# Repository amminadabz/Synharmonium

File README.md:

# The Synharmonium

#### is a new kind of musical instrument.
Designed to be easy to use, and more importantly, easy to make good music with. It uses the accordion's Stradella bass system to make it easy to play notes and chords that go well together, the Omnichord's strum plate to give texture to that harmony, and a piano keyboard for a familiar way to add a melody.

## A Well-Tempered synthesizer.
One of the goals of the Synharmonium is to create an instrument which uses an algorithmic implementation of just intonation. In other words, it tunes every note in a perfect mathematical relation to the root of whatever chord is being played. Where other instruments simply have every note an equal distance apart and call it done ("Equal Temperament"), the Synharmonium will ensure they are always in simple ratios to each other, allowing for a more resonant sound. But if you want to play _with_ those other instruments, you always have the option to disable this feature and return to the more common tuning.

## Digital where it's needed, analogue where it counts.
The Synharmonium uses a digital system to implement that tuning algorithm. But once the computer has decided what frequencies are best, everything that can analogue will be, including the envelope generators, drum machine oscillators, and effects. This allows it to have that classic analogue sound with none of the downsides.

But, if you want to use the Synharmonium's tuning technology with an external synthesizer, it also has full MIDI compatibility (with both DIN and USB).

## Free to build, modify, and hack
The hardware and software are all open source. I intend to base the control and tuning systems on an Arduino, which is beginner-friendly and hackable by design. I haven't the means to build these machines on a large scale at the moment (though I've thought about selling an "official version" as a preassembled machine and a kit, lmk what y'all think), so for the time being I will just be providing the design for free. That means you get to build it (!) until I know what I'm doing.

## A work in progress.
I'll be real with y'all: I don't know what I'm doing. Every part of this project is a skill that I am learning as I go. But I think this is a thing that deserves to exist, so I intend to let it. It will probably take some time, as I am currently pursuing degrees in Electrical Engineering and Computer Engineering, so I can only work on the Synharmonium in my free time.

If you have skills that could help this process along, feel free to join the project. Do [send me an email](mailto:uiwmusic@proton.me) first though, I'd like to know who I'm working with! 

Here goes nothin'!

-Evan

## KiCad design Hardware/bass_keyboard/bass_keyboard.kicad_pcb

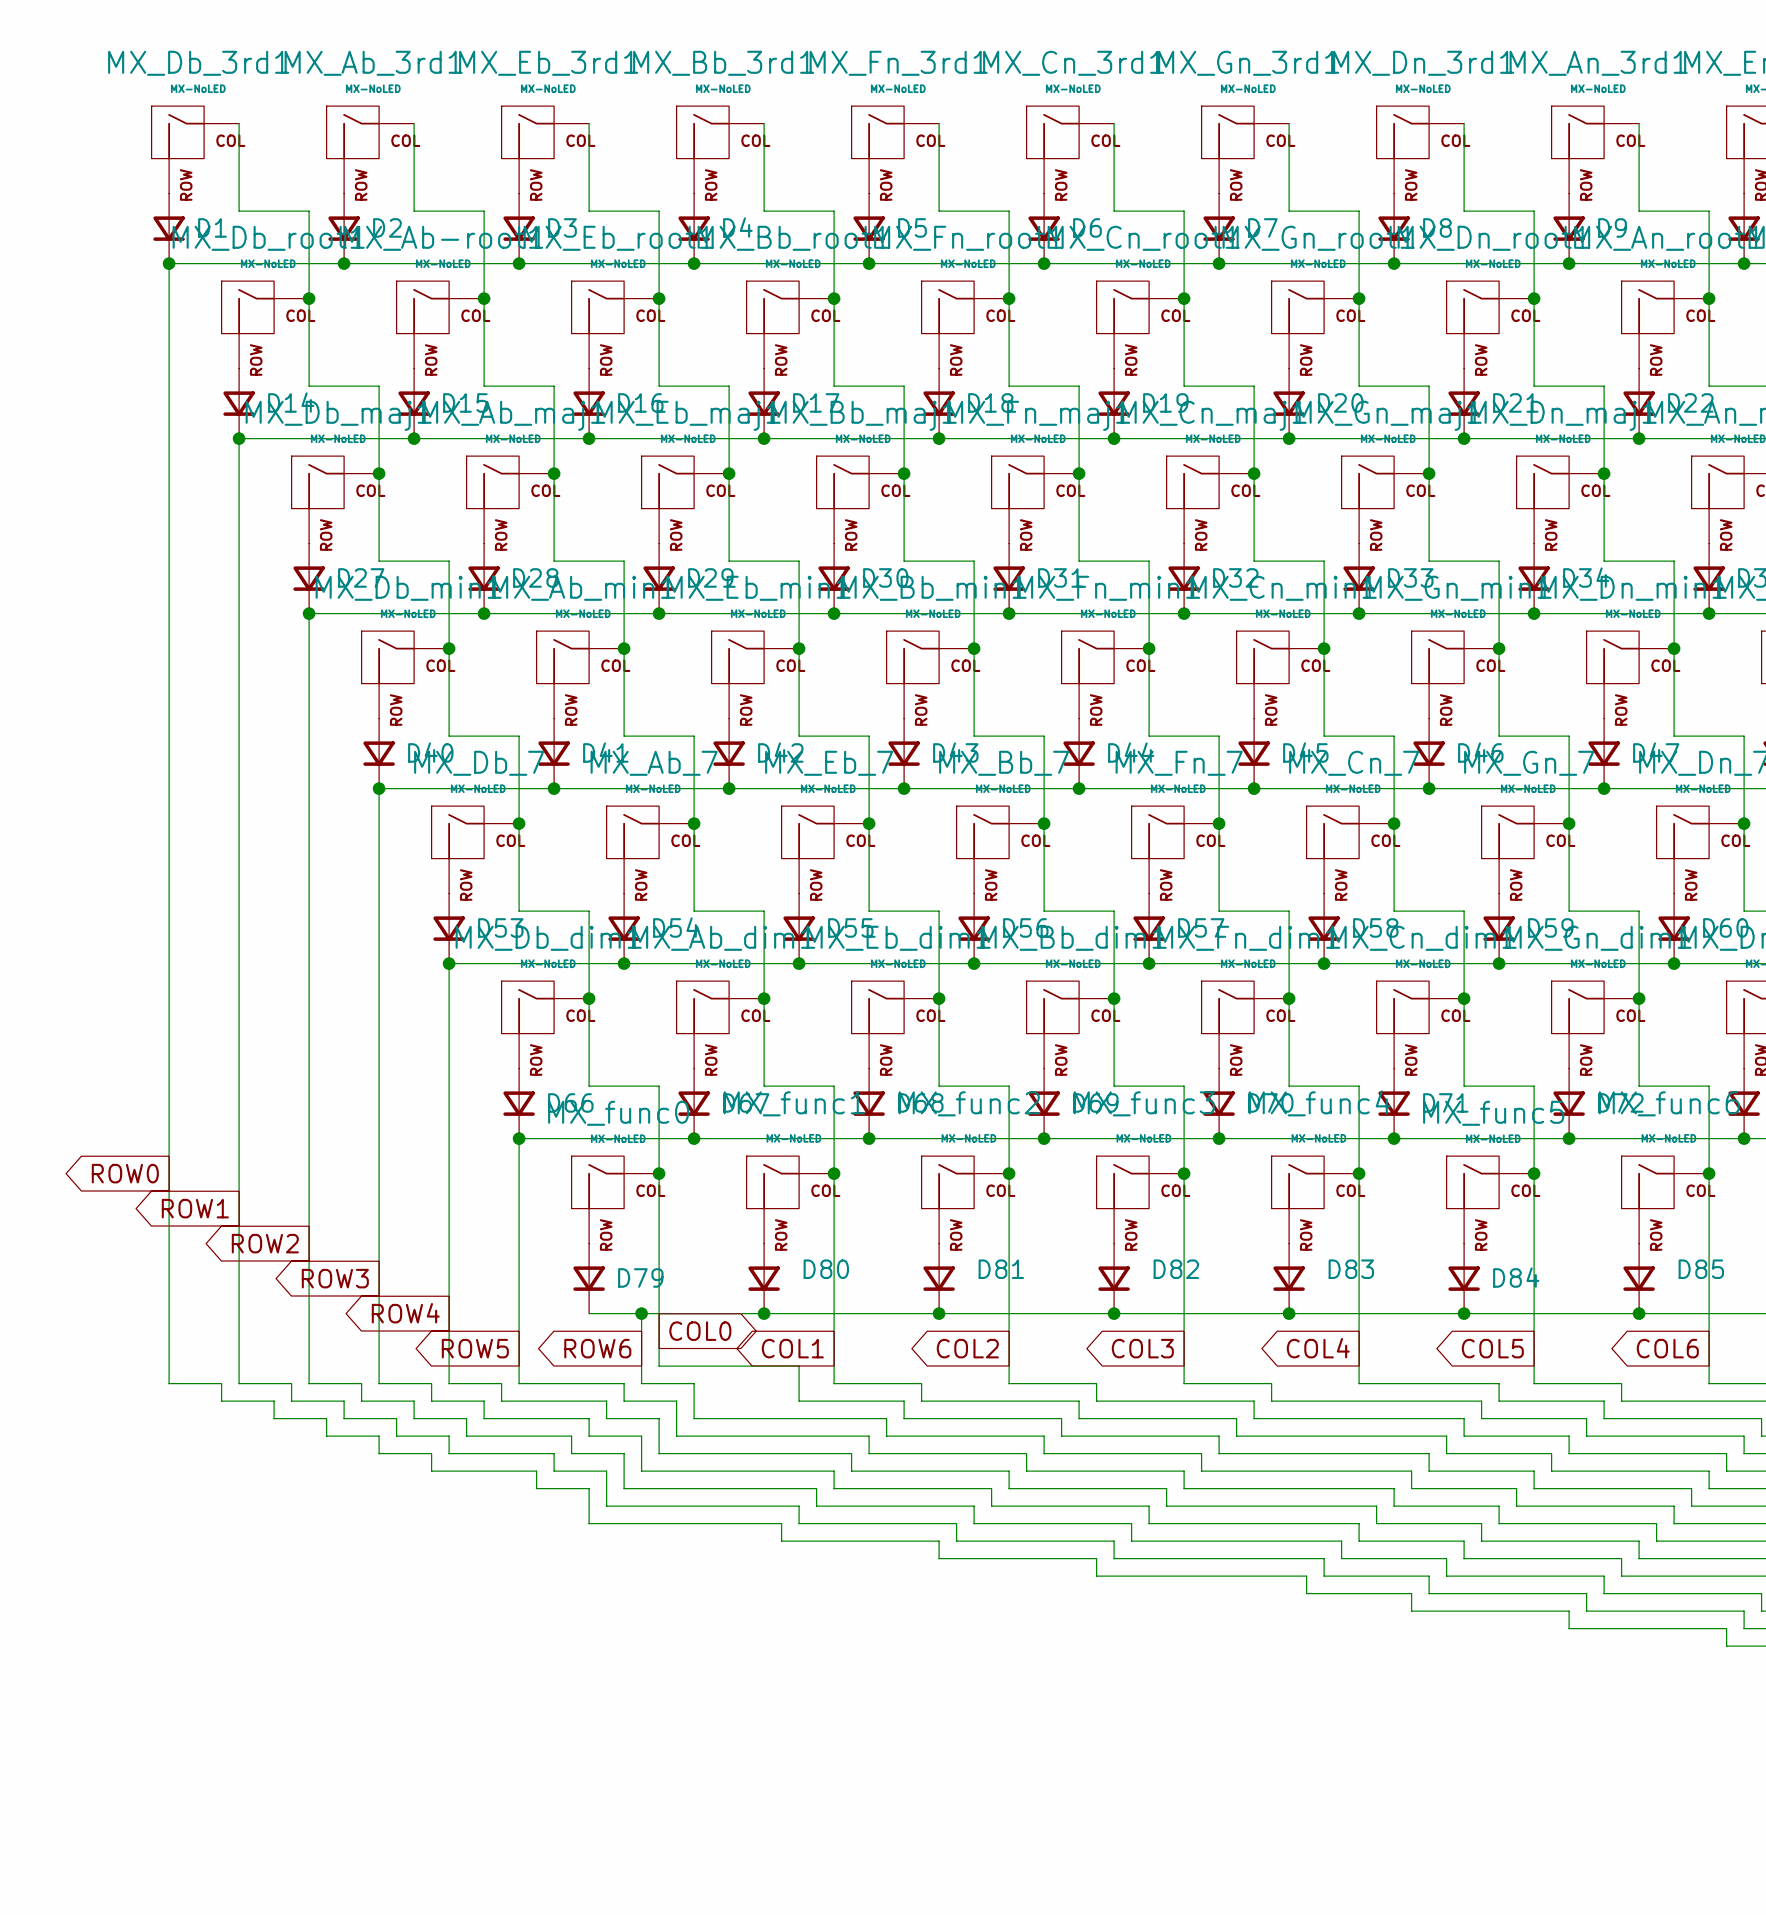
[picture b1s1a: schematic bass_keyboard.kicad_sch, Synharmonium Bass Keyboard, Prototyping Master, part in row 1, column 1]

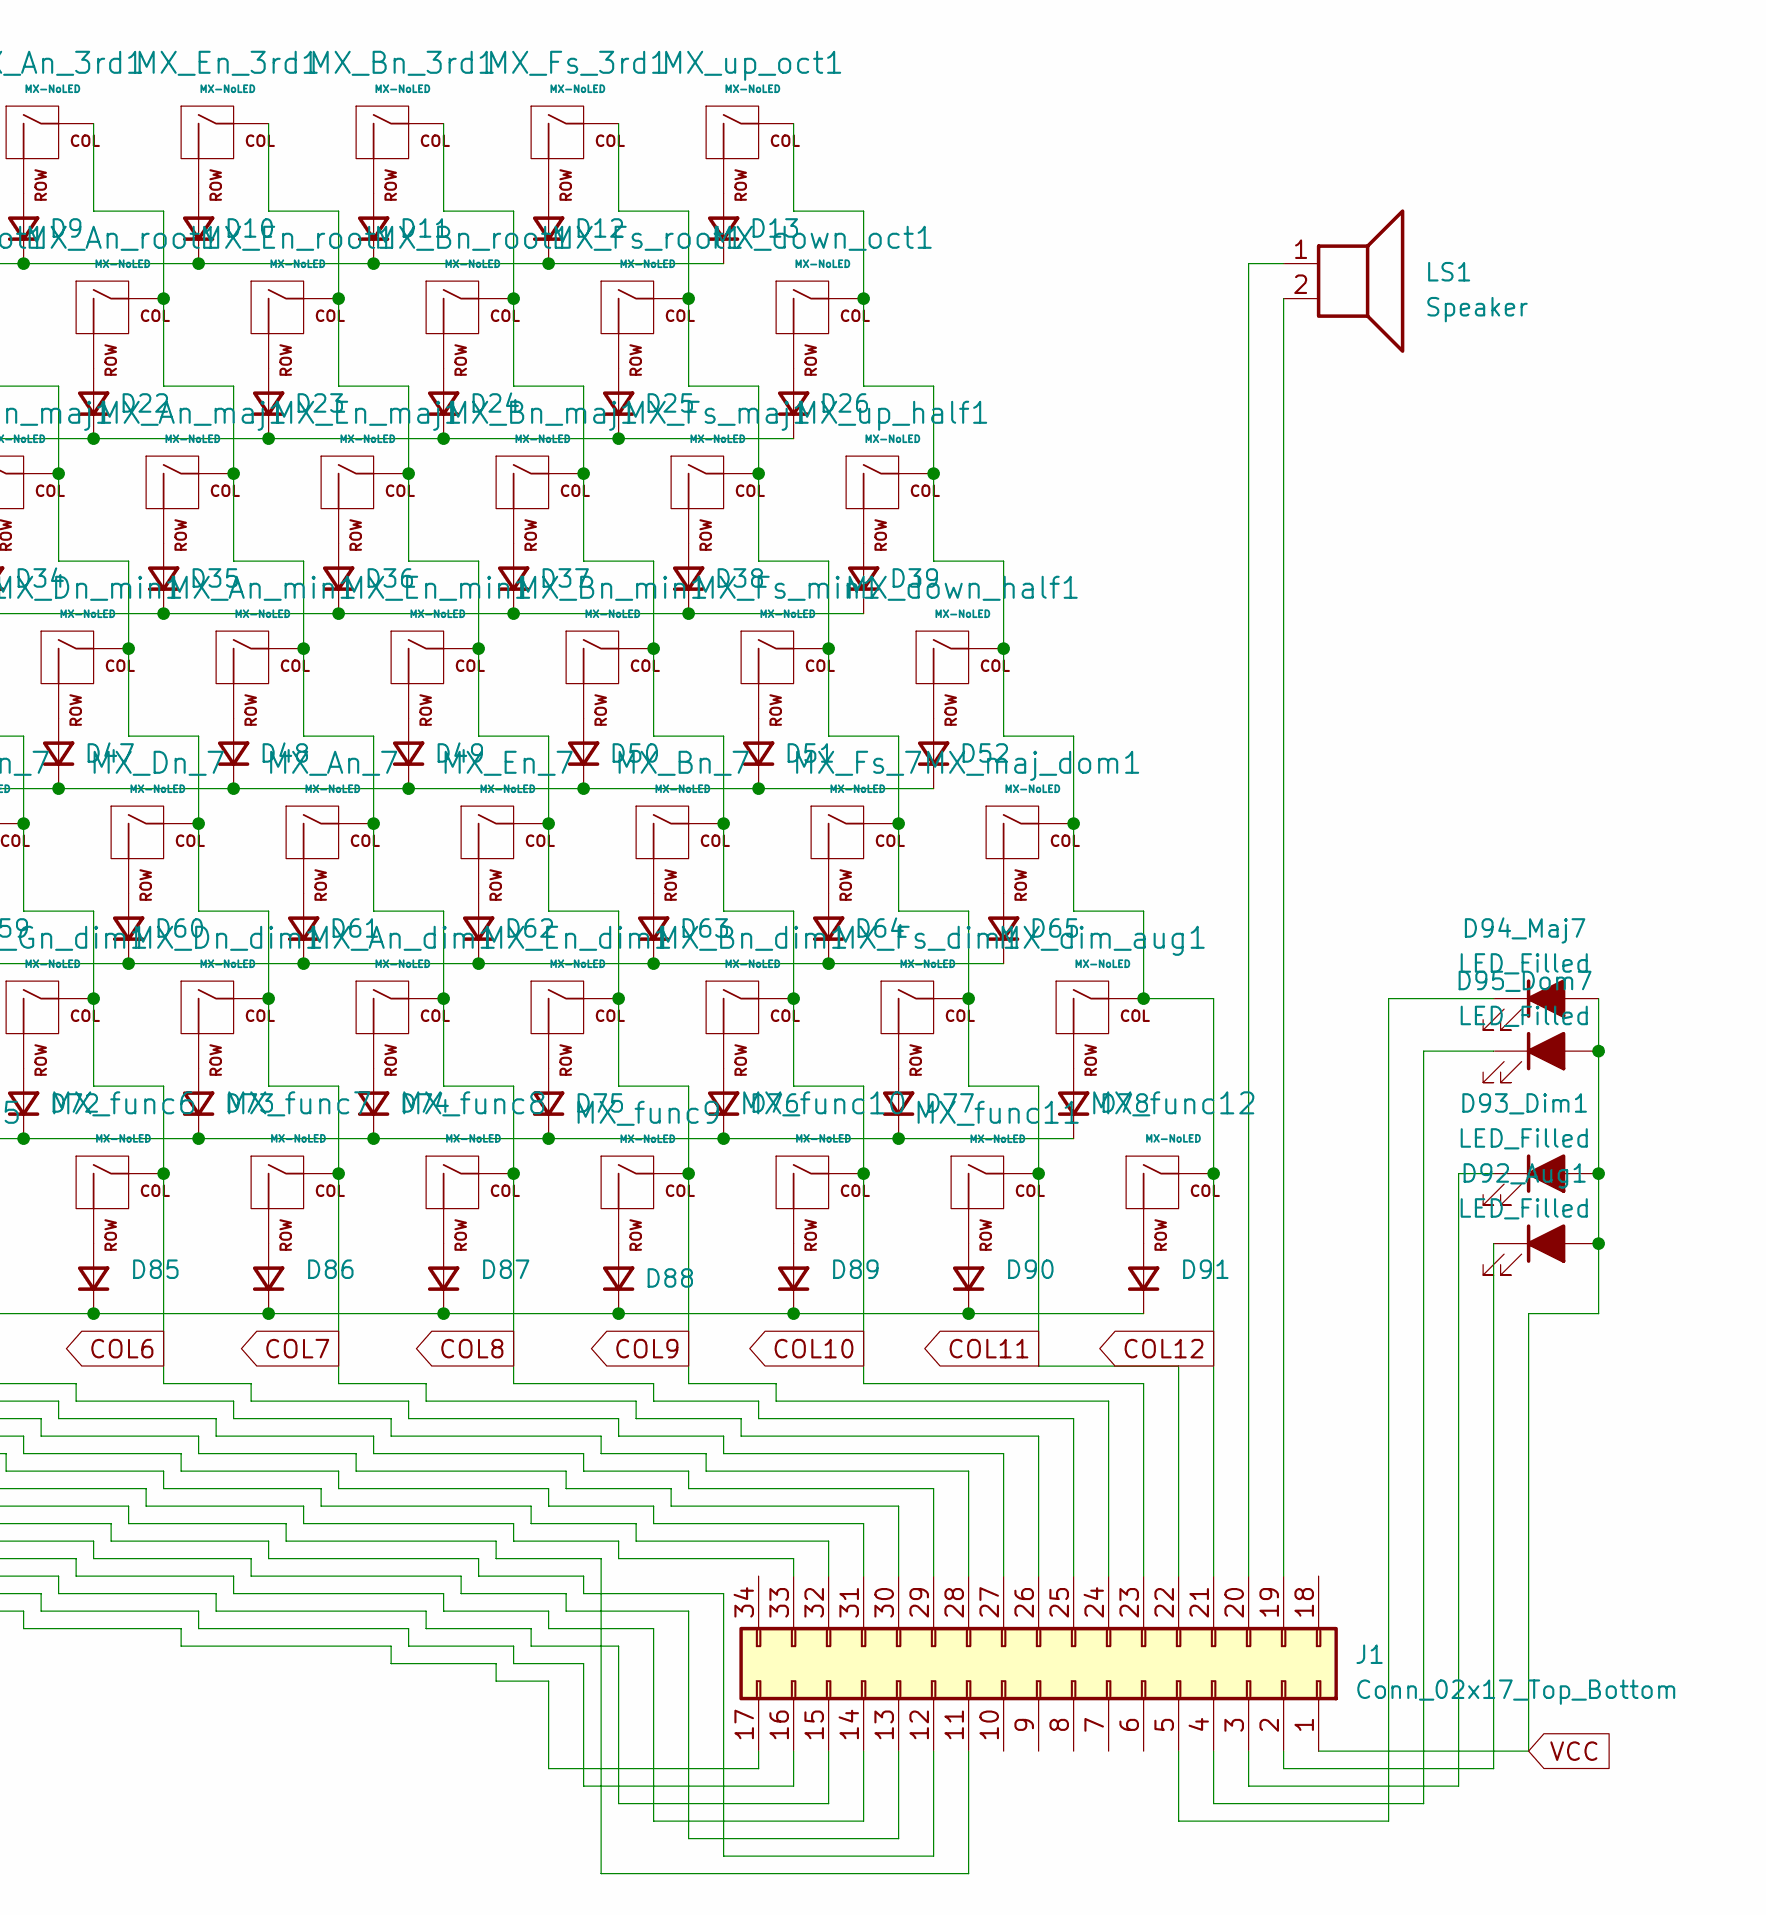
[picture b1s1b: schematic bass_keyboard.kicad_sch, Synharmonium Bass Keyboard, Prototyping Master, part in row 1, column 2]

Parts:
D1, D2, D3, D4, D5, D6, D7, D8, D9, D10, D11, D12, D13, D14, D15, D16, D17, D18, D19, D20, D21, D22, D23, D24, D25, D26, D27, D28, D29, D30, D31, D32, D33, D34, D35, D36, D37, D38, D39, D40, D41, D42, D43, D44, D45, D46, D47, D48, D49, D50, D51, D52, D53, D54, D55, D56, D57, D58, D59, D60, D61, D62, D63, D64, D65, D66, D67, D68, D69, D70, D71, D72, D73, D74, D75, D76, D77, D78, D79, D80, D81, D82, D83, D84, D85, D86, D87, D88, D89, D90, D91: D_Small; D_SOD-123
D92_Aug1, D93_Dim1, D94_Maj7, D95_Dom7: LED_Filled; LED_D3.0mm-Pretty
J1: Conn_02x17_Top_Bottom; IDC-Header_2x17_P2.54mm_Vertical
LS1: Speaker; SolderWire-1sqmm_1x02_P5.4mm_D1.4mm_OD2.7mm
MX_Ab-root1: MX-NoLED; SW_Cherry_MX_1.00u_PCB
MX_Ab_3rd1, MX_Ab_7: MX-NoLED; SW_Cherry_MX_1.00u_PCB
MX_Ab_dim1: MX-NoLED; SW_Cherry_MX_1.00u_PCB
MX_Ab_maj1: MX-NoLED; SW_Cherry_MX_1.00u_PCB
MX_Ab_min1: MX-NoLED; SW_Cherry_MX_1.00u_PCB
MX_An_3rd1, MX_An_7: MX-NoLED; SW_Cherry_MX_1.00u_PCB
MX_An_dim1: MX-NoLED; SW_Cherry_MX_1.00u_PCB
MX_An_maj1: MX-NoLED; SW_Cherry_MX_1.00u_PCB
MX_An_min1: MX-NoLED; SW_Cherry_MX_1.00u_PCB
MX_An_root1: MX-NoLED; SW_Cherry_MX_1.00u_PCB
MX_Bb_3rd1, MX_Bb_7: MX-NoLED; SW_Cherry_MX_1.00u_PCB
MX_Bb_dim1: MX-NoLED; SW_Cherry_MX_1.00u_PCB
MX_Bb_maj1: MX-NoLED; SW_Cherry_MX_1.00u_PCB
MX_Bb_min1: MX-NoLED; SW_Cherry_MX_1.00u_PCB
MX_Bb_root1: MX-NoLED; SW_Cherry_MX_1.00u_PCB
MX_Bn_3rd1, MX_Bn_7: MX-NoLED; SW_Cherry_MX_1.00u_PCB
MX_Bn_dim1: MX-NoLED; SW_Cherry_MX_1.00u_PCB
MX_Bn_maj1: MX-NoLED; SW_Cherry_MX_1.00u_PCB
MX_Bn_min1: MX-NoLED; SW_Cherry_MX_1.00u_PCB
MX_Bn_root1: MX-NoLED; SW_Cherry_MX_1.00u_PCB
MX_Cn_3rd1, MX_Cn_7: MX-NoLED; SW_Cherry_MX_1.00u_PCB
MX_Cn_dim1: MX-NoLED; SW_Cherry_MX_1.00u_PCB
MX_Cn_maj1: MX-NoLED; SW_Cherry_MX_1.00u_PCB
MX_Cn_min1: MX-NoLED; SW_Cherry_MX_1.00u_PCB
MX_Cn_root1: MX-NoLED; SW_Cherry_MX_1.00u_PCB
MX_Db_3rd1, MX_Db_7: MX-NoLED; SW_Cherry_MX_1.00u_PCB
MX_Db_dim1: MX-NoLED; SW_Cherry_MX_1.00u_PCB
MX_Db_maj1: MX-NoLED; SW_Cherry_MX_1.00u_PCB
MX_Db_min1: MX-NoLED; SW_Cherry_MX_1.00u_PCB
MX_Db_root1: MX-NoLED; SW_Cherry_MX_1.00u_PCB
MX_Dn_3rd1, MX_Dn_7: MX-NoLED; SW_Cherry_MX_1.00u_PCB
MX_Dn_dim1: MX-NoLED; SW_Cherry_MX_1.00u_PCB
MX_Dn_maj1: MX-NoLED; SW_Cherry_MX_1.00u_PCB
MX_Dn_min1: MX-NoLED; SW_Cherry_MX_1.00u_PCB
MX_Dn_root1: MX-NoLED; SW_Cherry_MX_1.00u_PCB
MX_Eb_3rd1, MX_Eb_7: MX-NoLED; SW_Cherry_MX_1.00u_PCB
MX_Eb_dim1: MX-NoLED; SW_Cherry_MX_1.00u_PCB
MX_Eb_maj1: MX-NoLED; SW_Cherry_MX_1.00u_PCB
MX_Eb_min1: MX-NoLED; SW_Cherry_MX_1.00u_PCB
MX_Eb_root1: MX-NoLED; SW_Cherry_MX_1.00u_PCB
MX_En_3rd1, MX_En_7: MX-NoLED; SW_Cherry_MX_1.00u_PCB
MX_En_dim1: MX-NoLED; SW_Cherry_MX_1.00u_PCB
MX_En_maj1: MX-NoLED; SW_Cherry_MX_1.00u_PCB
MX_En_min1: MX-NoLED; SW_Cherry_MX_1.00u_PCB
MX_En_root1: MX-NoLED; SW_Cherry_MX_1.00u_PCB
MX_Fn_3rd1, MX_Fn_7: MX-NoLED; SW_Cherry_MX_1.00u_PCB
MX_Fn_dim1: MX-NoLED; SW_Cherry_MX_1.00u_PCB
MX_Fn_maj1: MX-NoLED; SW_Cherry_MX_1.00u_PCB
MX_Fn_min1: MX-NoLED; SW_Cherry_MX_1.00u_PCB
MX_Fn_root1: MX-NoLED; SW_Cherry_MX_1.00u_PCB
MX_Fs_3rd1, MX_Fs_7: MX-NoLED; SW_Cherry_MX_1.00u_PCB
MX_Fs_dim1: MX-NoLED; SW_Cherry_MX_1.00u_PCB
MX_Fs_maj1: MX-NoLED; SW_Cherry_MX_1.00u_PCB
MX_Fs_min1: MX-NoLED; SW_Cherry_MX_1.00u_PCB
MX_Fs_root1: MX-NoLED; SW_Cherry_MX_1.00u_PCB
MX_Gn_3rd1, MX_Gn_7: MX-NoLED; SW_Cherry_MX_1.00u_PCB
MX_Gn_dim1: MX-NoLED; SW_Cherry_MX_1.00u_PCB
MX_Gn_maj1: MX-NoLED; SW_Cherry_MX_1.00u_PCB
MX_Gn_min1: MX-NoLED; SW_Cherry_MX_1.00u_PCB
MX_Gn_root1: MX-NoLED; SW_Cherry_MX_1.00u_PCB
MX_dim_aug1: MX-NoLED; SW_Cherry_MX_1.00u_PCB
MX_down_half1: MX-NoLED; SW_Cherry_MX_1.00u_PCB
MX_down_oct1: MX-NoLED; SW_Cherry_MX_1.00u_PCB
MX_func0, MX_func1, MX_func2, MX_func3, MX_func4, MX_func5, MX_func6, MX_func7, MX_func8, MX_func9, MX_func10, MX_func11, MX_func12: MX-NoLED; SW_Cherry_MX_1.00u_PCB
MX_maj_dom1: MX-NoLED; SW_Cherry_MX_1.00u_PCB
MX_up_half1: MX-NoLED; SW_Cherry_MX_1.00u_PCB
MX_up_oct1: MX-NoLED; SW_Cherry_MX_1.00u_PCB

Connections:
COL0: J1.33, MX_Db_3rd1.1 (COL), MX_Db_7.1 (COL), MX_Db_dim1.1 (COL), MX_Db_maj1.1 (COL), MX_Db_min1.1 (COL), MX_Db_root1.1 (COL), MX_func0.1 (COL)
COL1: J1.32, MX_Ab-root1.1 (COL), MX_Ab_3rd1.1 (COL), MX_Ab_7.1 (COL), MX_Ab_dim1.1 (COL), MX_Ab_maj1.1 (COL), MX_Ab_min1.1 (COL), MX_func1.1 (COL)
COL2: J1.31, MX_Eb_3rd1.1 (COL), MX_Eb_7.1 (COL), MX_Eb_dim1.1 (COL), MX_Eb_maj1.1 (COL), MX_Eb_min1.1 (COL), MX_Eb_root1.1 (COL), MX_func2.1 (COL)
COL3: J1.30, MX_Bb_3rd1.1 (COL), MX_Bb_7.1 (COL), MX_Bb_dim1.1 (COL), MX_Bb_maj1.1 (COL), MX_Bb_min1.1 (COL), MX_Bb_root1.1 (COL), MX_func3.1 (COL)
COL4: J1.29, MX_Fn_3rd1.1 (COL), MX_Fn_7.1 (COL), MX_Fn_dim1.1 (COL), MX_Fn_maj1.1 (COL), MX_Fn_min1.1 (COL), MX_Fn_root1.1 (COL), MX_func4.1 (COL)
COL5: J1.28, MX_Cn_3rd1.1 (COL), MX_Cn_7.1 (COL), MX_Cn_dim1.1 (COL), MX_Cn_maj1.1 (COL), MX_Cn_min1.1 (COL), MX_Cn_root1.1 (COL), MX_func5.1 (COL)
COL6: J1.27, MX_Gn_3rd1.1 (COL), MX_Gn_7.1 (COL), MX_Gn_dim1.1 (COL), MX_Gn_maj1.1 (COL), MX_Gn_min1.1 (COL), MX_Gn_root1.1 (COL), MX_func6.1 (COL)
COL7: J1.26, MX_Dn_3rd1.1 (COL), MX_Dn_7.1 (COL), MX_Dn_dim1.1 (COL), MX_Dn_maj1.1 (COL), MX_Dn_min1.1 (COL), MX_Dn_root1.1 (COL), MX_func7.1 (COL)
COL8: J1.25, MX_An_3rd1.1 (COL), MX_An_7.1 (COL), MX_An_dim1.1 (COL), MX_An_maj1.1 (COL), MX_An_min1.1 (COL), MX_An_root1.1 (COL), MX_func8.1 (COL)
COL9: J1.24, MX_En_3rd1.1 (COL), MX_En_7.1 (COL), MX_En_dim1.1 (COL), MX_En_maj1.1 (COL), MX_En_min1.1 (COL), MX_En_root1.1 (COL), MX_func9.1 (COL)
COL10: J1.23, MX_Bn_3rd1.1 (COL), MX_Bn_7.1 (COL), MX_Bn_dim1.1 (COL), MX_Bn_maj1.1 (COL), MX_Bn_min1.1 (COL), MX_Bn_root1.1 (COL), MX_func10.1 (COL)
COL11: J1.22, MX_Fs_3rd1.1 (COL), MX_Fs_7.1 (COL), MX_Fs_dim1.1 (COL), MX_Fs_maj1.1 (COL), MX_Fs_min1.1 (COL), MX_Fs_root1.1 (COL), MX_func11.1 (COL)
COL12: J1.21, MX_dim_aug1.1 (COL), MX_down_half1.1 (COL), MX_down_oct1.1 (COL), MX_func12.1 (COL), MX_maj_dom1.1 (COL), MX_up_half1.1 (COL), MX_up_oct1.1 (COL)
unnamed: D1.2 (A), MX_Db_3rd1.2 (ROW)
unnamed: D2.2 (A), MX_Ab_3rd1.2 (ROW)
unnamed: D3.2 (A), MX_Eb_3rd1.2 (ROW)
unnamed: D4.2 (A), MX_Bb_3rd1.2 (ROW)
unnamed: D5.2 (A), MX_Fn_3rd1.2 (ROW)
unnamed: D6.2 (A), MX_Cn_3rd1.2 (ROW)
unnamed: D7.2 (A), MX_Gn_3rd1.2 (ROW)
unnamed: D8.2 (A), MX_Dn_3rd1.2 (ROW)
unnamed: D9.2 (A), MX_An_3rd1.2 (ROW)
unnamed: D10.2 (A), MX_En_3rd1.2 (ROW)
unnamed: D11.2 (A), MX_Bn_3rd1.2 (ROW)
unnamed: D12.2 (A), MX_Fs_3rd1.2 (ROW)
unnamed: D13.2 (A), MX_up_oct1.2 (ROW)
unnamed: D14.2 (A), MX_Db_root1.2 (ROW)
unnamed: D15.2 (A), MX_Ab-root1.2 (ROW)
unnamed: D16.2 (A), MX_Eb_root1.2 (ROW)
unnamed: D17.2 (A), MX_Bb_root1.2 (ROW)
unnamed: D18.2 (A), MX_Fn_root1.2 (ROW)
unnamed: D19.2 (A), MX_Cn_root1.2 (ROW)
unnamed: D20.2 (A), MX_Gn_root1.2 (ROW)
unnamed: D21.2 (A), MX_Dn_root1.2 (ROW)
unnamed: D22.2 (A), MX_An_root1.2 (ROW)
unnamed: D23.2 (A), MX_En_root1.2 (ROW)
unnamed: D24.2 (A), MX_Bn_root1.2 (ROW)
unnamed: D25.2 (A), MX_Fs_root1.2 (ROW)
unnamed: D26.2 (A), MX_down_oct1.2 (ROW)
unnamed: D27.2 (A), MX_Db_maj1.2 (ROW)
unnamed: D28.2 (A), MX_Ab_maj1.2 (ROW)
unnamed: D29.2 (A), MX_Eb_maj1.2 (ROW)
unnamed: D30.2 (A), MX_Bb_maj1.2 (ROW)
unnamed: D31.2 (A), MX_Fn_maj1.2 (ROW)
unnamed: D32.2 (A), MX_Cn_maj1.2 (ROW)
unnamed: D33.2 (A), MX_Gn_maj1.2 (ROW)
unnamed: D34.2 (A), MX_Dn_maj1.2 (ROW)
unnamed: D35.2 (A), MX_An_maj1.2 (ROW)
unnamed: D36.2 (A), MX_En_maj1.2 (ROW)
unnamed: D37.2 (A), MX_Bn_maj1.2 (ROW)
unnamed: D38.2 (A), MX_Fs_maj1.2 (ROW)
unnamed: D39.2 (A), MX_up_half1.2 (ROW)
unnamed: D40.2 (A), MX_Db_min1.2 (ROW)
unnamed: D41.2 (A), MX_Ab_min1.2 (ROW)
unnamed: D42.2 (A), MX_Eb_min1.2 (ROW)
unnamed: D43.2 (A), MX_Bb_min1.2 (ROW)
unnamed: D44.2 (A), MX_Fn_min1.2 (ROW)
unnamed: D45.2 (A), MX_Cn_min1.2 (ROW)
unnamed: D46.2 (A), MX_Gn_min1.2 (ROW)
unnamed: D47.2 (A), MX_Dn_min1.2 (ROW)
unnamed: D48.2 (A), MX_An_min1.2 (ROW)
unnamed: D49.2 (A), MX_En_min1.2 (ROW)
unnamed: D50.2 (A), MX_Bn_min1.2 (ROW)
unnamed: D51.2 (A), MX_Fs_min1.2 (ROW)
unnamed: D52.2 (A), MX_down_half1.2 (ROW)
unnamed: D53.2 (A), MX_Db_7.2 (ROW)
unnamed: D54.2 (A), MX_Ab_7.2 (ROW)
unnamed: D55.2 (A), MX_Eb_7.2 (ROW)
unnamed: D56.2 (A), MX_Bb_7.2 (ROW)
unnamed: D57.2 (A), MX_Fn_7.2 (ROW)
unnamed: D58.2 (A), MX_Cn_7.2 (ROW)
unnamed: D59.2 (A), MX_Gn_7.2 (ROW)
unnamed: D60.2 (A), MX_Dn_7.2 (ROW)
unnamed: D61.2 (A), MX_An_7.2 (ROW)
unnamed: D62.2 (A), MX_En_7.2 (ROW)
unnamed: D63.2 (A), MX_Bn_7.2 (ROW)
unnamed: D64.2 (A), MX_Fs_7.2 (ROW)
unnamed: D65.2 (A), MX_maj_dom1.2 (ROW)
unnamed: D66.2 (A), MX_Db_dim1.2 (ROW)
unnamed: D67.2 (A), MX_Ab_dim1.2 (ROW)
unnamed: D68.2 (A), MX_Eb_dim1.2 (ROW)
unnamed: D69.2 (A), MX_Bb_dim1.2 (ROW)
unnamed: D70.2 (A), MX_Fn_dim1.2 (ROW)
unnamed: D71.2 (A), MX_Cn_dim1.2 (ROW)
unnamed: D72.2 (A), MX_Gn_dim1.2 (ROW)
unnamed: D73.2 (A), MX_Dn_dim1.2 (ROW)
unnamed: D74.2 (A), MX_An_dim1.2 (ROW)
unnamed: D75.2 (A), MX_En_dim1.2 (ROW)
unnamed: D76.2 (A), MX_Bn_dim1.2 (ROW)
unnamed: D77.2 (A), MX_Fs_dim1.2 (ROW)
unnamed: D78.2 (A), MX_dim_aug1.2 (ROW)
unnamed: D79.2 (A), MX_func0.2 (ROW)
unnamed: D80.2 (A), MX_func1.2 (ROW)
unnamed: D81.2 (A), MX_func2.2 (ROW)
unnamed: D82.2 (A), MX_func3.2 (ROW)
unnamed: D83.2 (A), MX_func4.2 (ROW)
unnamed: D84.2 (A), MX_func5.2 (ROW)
unnamed: D85.2 (A), MX_func6.2 (ROW)
unnamed: D86.2 (A), MX_func7.2 (ROW)
unnamed: D87.2 (A), MX_func8.2 (ROW)
unnamed: D88.2 (A), MX_func9.2 (ROW)
unnamed: D89.2 (A), MX_func10.2 (ROW)
unnamed: D90.2 (A), MX_func11.2 (ROW)
unnamed: D91.2 (A), MX_func12.2 (ROW)
unnamed: D92_Aug1.1 (K), J1.2
unnamed: D93_Dim1.1 (K), J1.3
unnamed: D94_Maj7.1 (K), J1.5
unnamed: D95_Dom7.1 (K), J1.4
unnamed: J1.19, LS1.2
unnamed: J1.20, LS1.1
ROW0: D1.1 (K), D2.1 (K), D3.1 (K), D4.1 (K), D5.1 (K), D6.1 (K), D7.1 (K), D8.1 (K), D9.1 (K), D10.1 (K), D11.1 (K), D12.1 (K), D13.1 (K), J1.17
ROW1: D14.1 (K), D15.1 (K), D16.1 (K), D17.1 (K), D18.1 (K), D19.1 (K), D20.1 (K), D21.1 (K), D22.1 (K), D23.1 (K), D24.1 (K), D25.1 (K), D26.1 (K), J1.16
ROW2: D27.1 (K), D28.1 (K), D29.1 (K), D30.1 (K), D31.1 (K), D32.1 (K), D33.1 (K), D34.1 (K), D35.1 (K), D36.1 (K), D37.1 (K), D38.1 (K), D39.1 (K), J1.15
ROW3: D40.1 (K), D41.1 (K), D42.1 (K), D43.1 (K), D44.1 (K), D45.1 (K), D46.1 (K), D47.1 (K), D48.1 (K), D49.1 (K), D50.1 (K), D51.1 (K), D52.1 (K), J1.14
ROW4: D53.1 (K), D54.1 (K), D55.1 (K), D56.1 (K), D57.1 (K), D58.1 (K), D59.1 (K), D60.1 (K), D61.1 (K), D62.1 (K), D63.1 (K), D64.1 (K), D65.1 (K), J1.13
ROW5: D66.1 (K), D67.1 (K), D68.1 (K), D69.1 (K), D70.1 (K), D71.1 (K), D72.1 (K), D73.1 (K), D74.1 (K), D75.1 (K), D76.1 (K), D77.1 (K), D78.1 (K), J1.12
ROW6: D79.1 (K), D80.1 (K), D81.1 (K), D82.1 (K), D83.1 (K), D84.1 (K), D85.1 (K), D86.1 (K), D87.1 (K), D88.1 (K), D89.1 (K), D90.1 (K), D91.1 (K), J1.11
VCC: D92_Aug1.2 (A), D93_Dim1.2 (A), D94_Maj7.2 (A), D95_Dom7.2 (A), J1.1

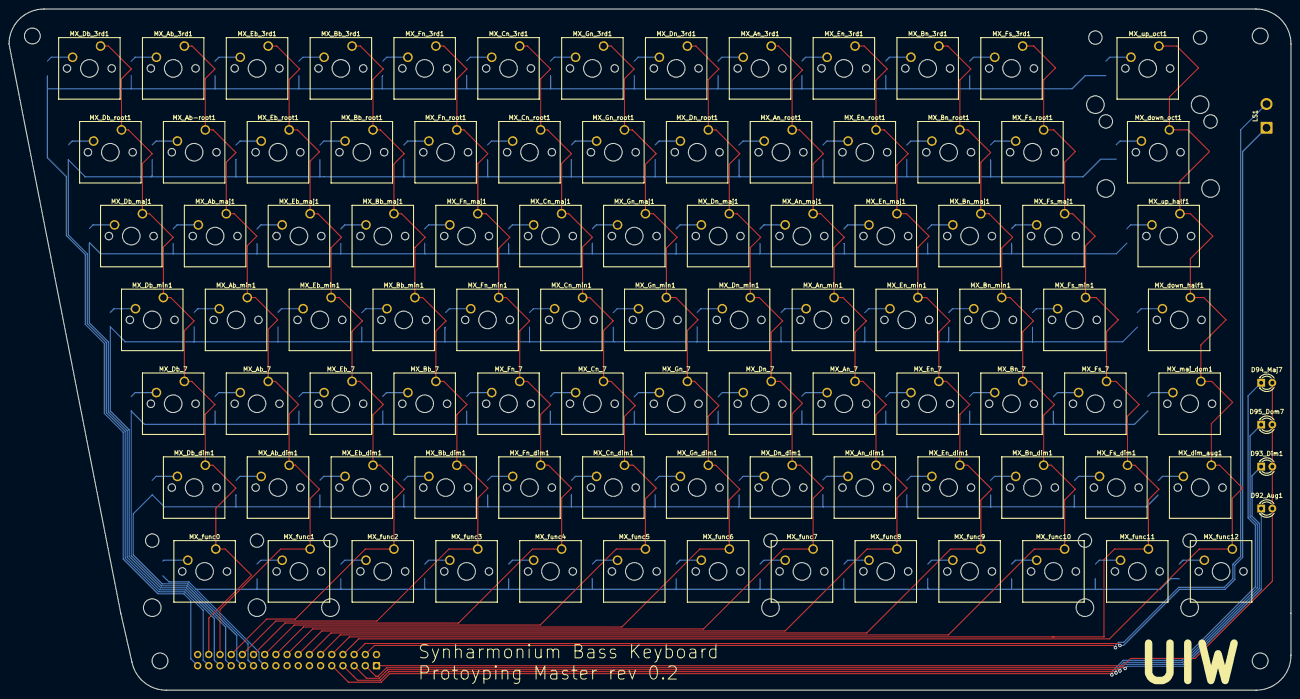
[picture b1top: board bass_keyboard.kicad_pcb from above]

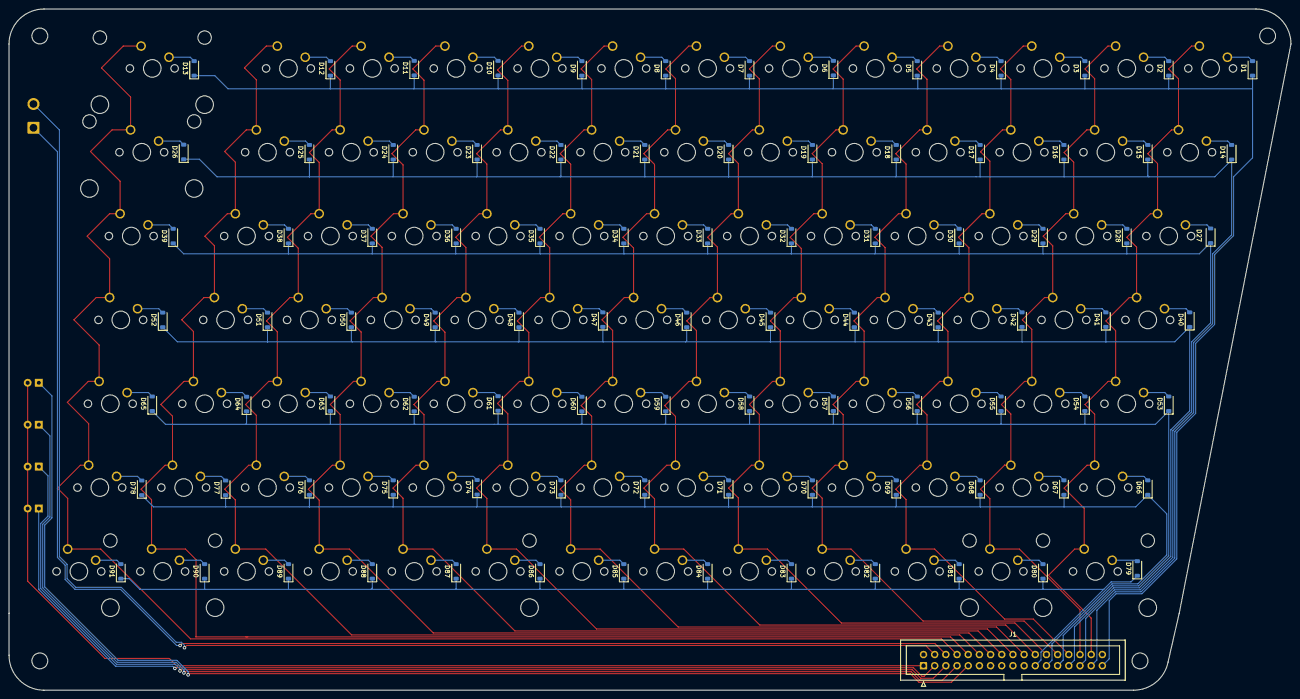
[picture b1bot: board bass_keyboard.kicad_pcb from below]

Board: 2 copper layers, 291.3 x 154.8 mm, 188 parts (92 on the bottom side), 118 nets.

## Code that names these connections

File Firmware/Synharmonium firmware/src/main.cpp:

#include <Arduino.h>
#include <Keypad.h>

const byte ROWS = 7; //seven rows
const byte COLS = 13; //thirteen columns
char bassKeys[ROWS][COLS] = {
    // there need to be more unique values here than i can type, so we're just using an array of 
    // hexes which fits into ascii space. the characters they represent don't really matter, and 
    // they will be converted to something usable once out of the keymatrix library.
    {'\x00','\x01','\x02','\x03','\x04','\x05','\x06','\x07','\x08','\x09','\x0A','\x0B','\x0C'},  // thirds, up octave
    {'\x10','\x11','\x12','\x13','\x14','\x15','\x16','\x17','\x18','\x19','\x1A','\x1B','\x1C'},  // roots, down octave
    {'\x20','\x21','\x22','\x23','\x24','\x25','\x26','\x27','\x28','\x29','\x2A','\x2B','\x2C'},  // major chords, up half step
    {'\x30','\x31','\x32','\x33','\x34','\x35','\x36','\x37','\x38','\x39','\x3A','\x3B','\x3C'},  // minor chords, down half step
    {'\x40','\x41','\x42','\x43','\x44','\x45','\x46','\x47','\x48','\x49','\x4A','\x4B','\x4C'},  // 7th chords, major 7th vs dominant 7th toggle
    {'\x50','\x51','\x52','\x53','\x54','\x55','\x56','\x57','\x58','\x59','\x5A','\x5B','\x5C'},  // diminished or augmented chords, toggle between the two
    {'\x60','\x61','\x62','\x63','\x64','\x65','\x66','\x67','\x68','\x69','\x6A','\x6B','\x6C'}   // function row
};
byte rowPins[ROWS] = {32, 31, 30, 29, 28, 27, 26}; //connect to the row pinouts of the keypad
byte colPins[COLS] = {45, 44, 43, 42, 41, 40, 39, 38, 37, 36, 35, 34, 33}; //connect to the column pinouts of the keypad

Keypad bassKeyboard = Keypad( makeKeymap(bassKeys), rowPins, colPins, ROWS, COLS );

unsigned long loopCount;
unsigned long startTime;
String msg;

// microcontroller pinout, see /hardware/pinout_r***.ods
  // bass keyboard
    #define d92   22
    #define d93   23
    #define d94   24
    #define d95   25
    
    // #define row0  32
    // #define row1  31
    // #define row2  30
    // #define row3  29
    // #define row4  28
    // #define row5  27
    // #define row6  26

    // #define col0  45
    // #define col1  44
    // #define col2  43
    // #define col3  42
    // #define col4  41
    // #define col5  40
    // #define col6  39
    // #define col7  38
    // #define col8  37
    // #define col9  36
    // #define col10 35
    // #define col11 34
    // #define col12 33



// put function declarations here:


void setup() {
    Serial.begin(9600);
    loopCount = 0;
    startTime = millis();
    msg = "";
}

void loop() {
    loopCount++;
    if ( (millis()-startTime)>5000 ) {
        Serial.print("Average loops per second = ");
        Serial.println(loopCount/5);
        startTime = millis();
        loopCount = 0;
    }

    // Fills bassKeyboard.key[ ] array with up-to 10 active keys.
    // Returns true if there are ANY active keys.
    if (bassKeyboard.getKeys())
    {
        for (int i=0; i<LIST_MAX; i++)   // Scan the whole key list.
        {
            if ( bassKeyboard.key[i].stateChanged )   // Only find keys that have changed state.
            {
                switch (bassKeyboard.key[i].kstate) {  // Report active key state : IDLE, PRESSED, HOLD, or RELEASED
                    case PRESSED:
                    msg = " PRESSED.";
                break;
                    case HOLD:
                    msg = " HOLD.";
                break;
                    case RELEASED:
                    msg = " RELEASED.";
                break;
                    case IDLE:
                    msg = " IDLE.";
                }
                Serial.print("Key ");
                Serial.print(bassKeyboard.key[i].kchar);
                Serial.println(msg);
            }
        }
    }
}

// put function definitions here:

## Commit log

2021-12-22 Add submodules for bass keyboard
2021-12-22 Added project-specific libraries
2021-12-23 Created switch matrix schematic
2021-12-23 Added sketches and mockups
2021-12-24 Added labels to switches
2021-12-26 Added footprints for diodes
    Having trouble finding the footprints for the switches
2022-01-07 Added female connector
    Added the connector for the cable to the logic module on the bass keyboard schematic
2022-02-06 Update files to Kicad 6
2022-03-24 Update README.md
    To better reflect more realistic design parameters.
2023-04-07 Future-proof bass keyboard
    Filled out the rest of the lower function row for futureproofing and expandability. Settled on a 2x16 pin header connector. Added indicator LEDs for the right side toggles, and speaker which is to be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
2023-04-08 Begin Bass Keyboard PCB design
    Started placing switch footprints for the root row.
2023-04-12 Finishing layout, routing
    Got all of the footprints where they need to be, created the pcb outline, and used Freerouting to route connections, doing some final connections by hand.
2023-04-12 Screwholes
    Added 4 screwholes at corners, tweaked bottom left corner.
2023-04-12 Silkscreen labels
    Added model, part name, logo
2023-04-12 Renders
    Replaced componentless led footprint with componentfull footprint. Rendered PCB with raytracing at a few angles.
2023-04-23 Added DSA Keycap models
2023-05-16 Redo traces on bass keyboard
    Completely started over on the traces, decided that the automatic routing was whack. Much happier with the new layout, increased orderliness and legibility, less prone to manufacturing error due to v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
2023-05-20 Starting on Firmware
    Fumbling blindly into platform.io, trying to get initial keyscanning and midi functionality
2023-05-22 Prepared keycaps for 3d printing
    sliced, diced, 3mf'd
2023-05-25 Added Website folder
    A custom web page will be hosted through github, and the source files will be stored here.
2023-05-28 Begin modeling piano keys, 3d printing adjustments
2023-05-28 Test
2023-05-28 Text File.txt
2023-05-28 index.html
2023-05-28 Update style.css
    Adding Corrected colors and fixing navbar
2023-05-29 Add renders
    Added renders of a possible finished project by @lucasminer on fiverr.
2023-05-29 Html edits
2023-05-29 Web update
2023-05-29 Revise paragraphs
2023-05-29 Adding Main page img and styling
2023-05-29 Add render model, optimize web image
2023-05-29 Created Logo and favicons
2023-05-30 Fixing Alignment issues of text
2023-05-30 Italic Test
2023-05-30 Update index.html
    Fixed Italic display issue
2023-05-31 Create about and contact pages, fill out top nav
2023-05-31 Update index.html
    writing in the features section
2023-05-31 Rename folder website to docs
2023-06-02 Website moved to separate repo
    see amminadabz.github.io
2023-06-20 Changed key matrix nomenclature
    see comment
2023-08-04 Explore alternatives for key matrix scanning
2023-10-09 Added Schematic PDF
2023-10-09 Update README.md
    Added image
